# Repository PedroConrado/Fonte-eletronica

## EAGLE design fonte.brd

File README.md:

# PROJETO: FONTE RETIFICADORA (3V-12V)
Trabalho desenvolvido no curso de Eletrônica para ciências de computação do professor Eduardo do Valle Simões.
Objetivos: Projeto de uma Fonte de Tensão entre 3V a 12V com capacidade de 100mA. Diagrama da Fonte com os valores dos componentes escolhidos e uma lista de componentes, contendo valores e preço.Link para o circuito no Falstad ou outro simulador. Projeto do Esquemático e do PCB no EAGLE. Se montou o circuito, incluir fotos da placa/protoboard. E um VIDEO mostrando o Projeto funcionando ou simulando, e explicando porque escolheu os valores dos componentes (Upa no Youtube e poe um link no teu Github).

## SCC0180 - Eletrônica para a Computação

## Desenvolvimento
Trabalho desenvolvido pelos alunos:
* Pedro Henrique Conrado Ferreira de Oliveira - 11819091
* Leonardo Chieppe - 9368730

## Vídeo Explicativo

## O Circuito 
Esquema do circuito, seguido de PBC. Os arquivos para o circuito estão disponíveis nesse mesmo repositório.

## Circuito Falstad
http://tinyurl.com/yd2tqbon

## Componentes
|Componente | Especificação | Justificativa |
|-----------|---------------|---------------|
|Transformador | 15v e 500mA | Responsável por transformar a tensão de 127V para 17V |
|Transistor NPN | 15v e 500mA | Permite controlar a passagem da corrente |
|Resistores x4 | 2Kohm, 1Kohm, 390ohm, 120ohm | Limitam a corrente de acordo com os demais componentes |
|Potenciômetro | 5Kohm | Regula a tensão da fonte entre 12V - 3V |
|Ponte retificadora | 1000V e 2A | Transforma a corrente alternada em corrente contínua |
|Capacitor | 470uF | Armazena corrente e libera quando a tensão interna é maior que a externa |
|Diodo de Zener | 0,5W | Opera mantendo a tensão máxima do circuito em 13V |

### Custo Unidade:
Transformador: [26,99](https://produto.mercadolivre.com.br/MLB-989866927-transformador-trafo-1515v-500ma-bivolt-eletronica-eletrica-_JM?quantity=1#position=1&type=item&tracking_id=b3b43099-b6d3-4246-a532-7356d0c044b9)
Transistor NPN: [0,17](https://www.baudaeletronica.com.br/transistor-npn-bc548.html)
Resistores: [0,13](https://produto.mercadolivre.com.br/MLB-1345217069-resistor-10k-ohms-100-unidades-_JM?quantity=1#position=2&type=item&tracking_id=ebb01ab1-c319-4e04-83d3-0f995a12885d)
Potenciômetro: [19,29](https://produto.mercadolivre.com.br/MLB-1441845757-potencimetro-multivoltas-baoter-3590s-2-502l-5k-_JM?quantity=1#position=2&type=item&tracking_id=554c0e8a-de74-48d3-8653-993a6cdda8ac)
Ponte retificadora: [4,78](https://www.usinainfo.com.br/pontes-retificadoras/ponte-retificadora-2w10-3938.html)
Capacitor: [0,57](https://www.baudaeletronica.com.br/capacitor-eletrolitico-470uf-35v.html)
Diodo de Zener: [0,13](https://www.baudaeletronica.com.br/diodo-zener-1n5231-5v1-0-5w.html)
##### Total: R$52,28

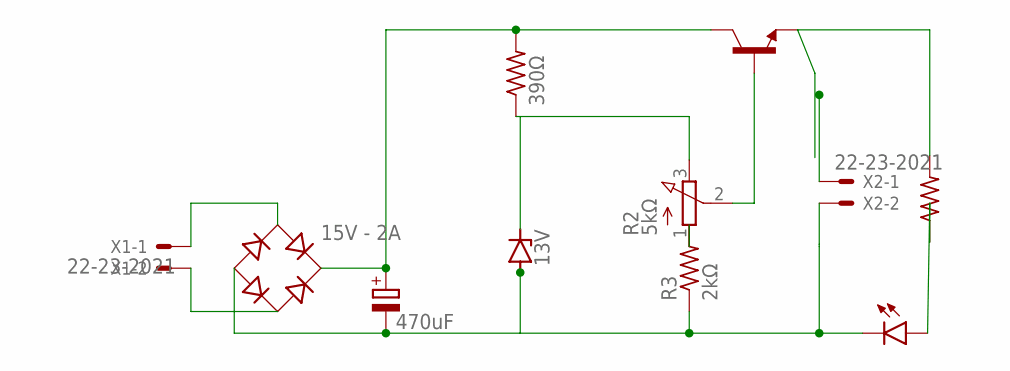
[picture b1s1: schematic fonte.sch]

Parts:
B1: 15V - 2A; RB1A
C1: 470uF; E3,5-10
D1: 13V; DO41Z10
LED1: LED5MM
Q1: BC547B; TO92
R1: 390Ω; 0309/12
R2: 5kΩ; 3RP/1610N
R3: 2kΩ; 0309/12
R5: R-US_0309/12; 0309/12
X1, X2: 22-23-2021

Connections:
unnamed: R2.1 (A), R3.2
unnamed: Q1.1 (E), R5.2, X2.1
unnamed: B1.AC2, X1.1
unnamed: B1.AC1, X1.2
unnamed: B1.-, C1.-, D1.A, LED1.K (C), R3.1, X2.2
unnamed: B1.+, C1.+, Q1.3 (C), R1.2
unnamed: R1.1, R2.3 (E)
unnamed: LED1.A, R5.1
unnamed: Q1.2 (B), R2.2 (S)

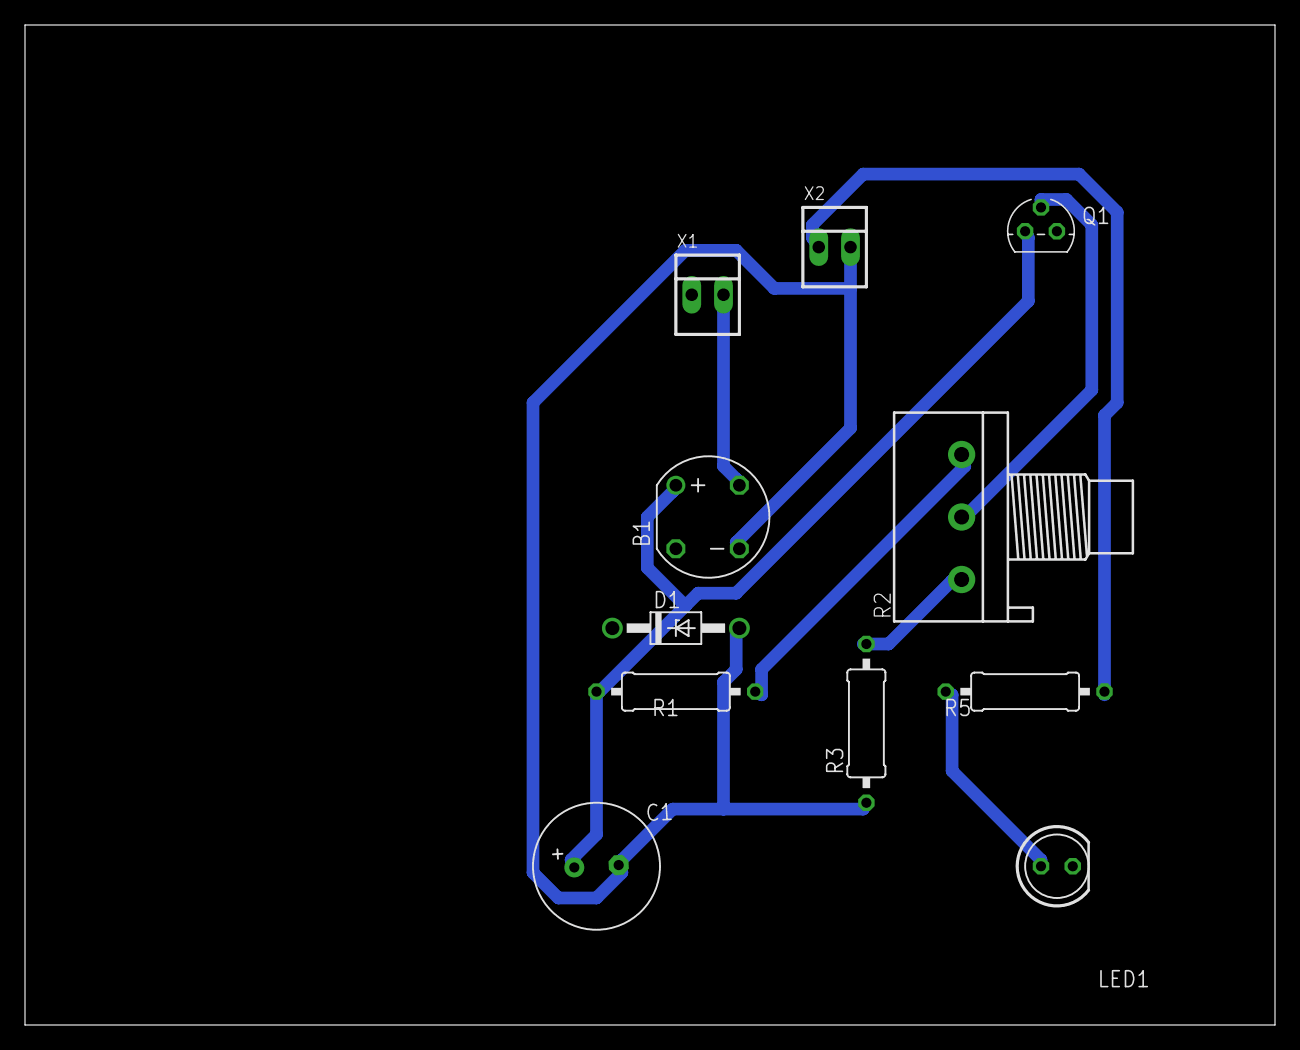
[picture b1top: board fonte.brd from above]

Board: 2 copper layers, 100.0 x 80.0 mm, 11 parts (0 on the bottom side), 9 nets.

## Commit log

2020-06-27 Create EAGLE
